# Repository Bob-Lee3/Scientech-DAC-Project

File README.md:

# Scientech-DAC-Project
Scientech DAC board prototype

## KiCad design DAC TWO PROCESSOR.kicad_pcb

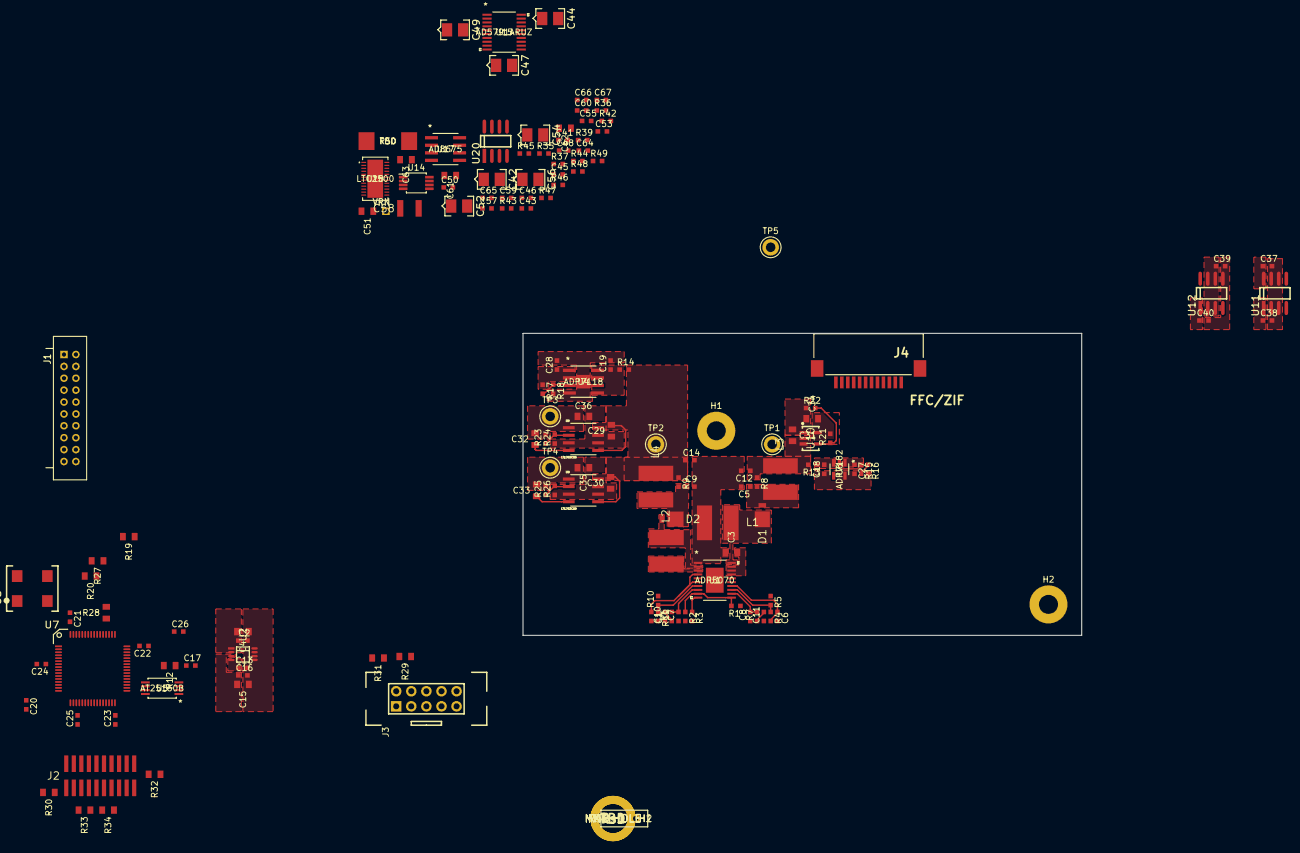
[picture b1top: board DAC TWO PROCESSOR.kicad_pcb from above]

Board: 4 copper layers, 94.0 x 50.8 mm, 155 parts (0 on the bottom side), 101 nets.

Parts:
C1, C6, C18, C19, C57, C59: 1uF; EIA0603
C2, C16, C17, C26, C41, C43, C45, C46, C48, C50, C53, C55, C64, C65, C66, C67: .1uF; EIA0603
C3, C4, C15, C34, C35, C36, C51: 10uF; EIA0805
C5, C12, C27, C28: 2.2uF; EIA0603
C7: 27pF; EIA0603
C8: 22pF; EIA0603
C9, C14, C25: 4.7uF; EIA0603
C10: .022uF; EIA0603
C11: .082uF; EIA0603
C13, C20, C21, C22, C23, C24, C60: .01uF; EIA0603
C29, C30, C31: 1uF; EIA0805
C32, C33: .01uF; EIA0805
C37, C38, C39, C40: .33uF; EIA0603
C42, C44, C47, C49, C52, C54, C56: 10uF; EIA3528
C58: 47uF X7R; EIA1210
C61, C62, C63: 6800pF; EIA0805
D1: BAT54LPS; MBRM120
D2: DFLS130-7; MBRM120
H1, H2: MNT_HOLE; HOLE188
H1#2, H2#2: MountingHole_Pad; MountingHole_3.2mm_M3_Pad
J1: CONN_20; ADAM_TECH_2FTR-20-SG
J2: CONN_10x2; SAMTEC_FTSH-110
J3: CONN_10; CON10
J4: FFC/ZIF; MOLEX_52207-1233
L1: 6.8uH; DR63
L2: 15uh; DR63
L3: 2.2uH; DR63
L4: 1.5uh; DR63
R1, R7: 30.1K; EIA0603
R2: 18.7K; EIA0603
R3: 49.9K; EIA0603
R4: 2.8K; EIA0603
R5: 54.9K; EIA0603
R6: 22K; EIA0603
R8, R13, R14: 10; EIA0603
R9: 4.7; EIA0603
R10: 63.4K; EIA0603
R11: 3.57K; EIA0603
R12: 220; EIA0805
R15, R17: 105K; EIA0603
R16, R18, R35, R36, R39, R42, R43, R44: 10K; EIA0603
R19, R20, R27, R28, R29, R30, R31, R32, R33, R34: 10K; EIA0805
R21, R25: 5.6K; EIA0603
R22, R24, R26: 1K; EIA0603
R23: 1.05K; EIA0603
R37: 5K; EIA0603
R38, R40, R41: 33; EIA0402
R45, R46: 30.1; EIA0603
R47, R48, R49: 0; EIA0603
R50: TBD; SMR3D
Rs1: TBD; Z201
TP1: VOUT2; TestPoint_Keystone_5010-5014_Multipurpose
TP2: VOUT1; TestPoint_Keystone_5010-5014_Multipurpose
TP3: +2.5V; TestPoint_Keystone_5010-5014_Multipurpose
TP4: +8V; TestPoint_Keystone_5010-5014_Multipurpose
TP5: -3V; TestPoint_Keystone_5010-5014_Multipurpose
TP7: VRN; TESTPOINT
U1: ADP5070; ADP5070AREZ
U2: REG113-3.3; REG113-33
U3: XX MHz; CB3
U4: ADP7118; ADP7118ARDZ
U5: AT25160B; AT25160B-XHL-B
U6: ADP7182; ADP7182AUJZ-2.5-R7
U7: STM32F7xx; TQFP50P-64
U8, U9: LT1763CS8; SO-8_S
U10: LT1964-SD; SOT23-5
U11: SM78L05; SOIC127P-8
U12: SM79L05; SOIC127P-8
U14: LT6655; MSOP65P-8
U15: AD5791ARUZ; AD5791BRUZ
U17: AD8675; AD8675ARZ-REEL7
U18: LTC2500; LTC2500CDKD-32-TRPBF
U20: OPA277; SOIC127P-8

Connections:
3.3V: C15.1, C16.1, C20.2, C21.2, C22.2, C24.2, C26.1, C46.2, C47.1, C60.1, J1.9, J2.1, R12.1, R20.1, U2.3, U5.7, U5.8, U7.13, U7.19, U7.32, U7.48, U7.64, U15.9, U15.10, U18.22
+2.5V: C32.1, C36.1, R23.2, TP3.1, U8.1
+5V: C38.1, J4.8, U11.1
+8V: C33.1, C35.1, R25.2, TP4.1, U9.1
+12V: C37.1, C64.1, C66.1, J1.17, J1.18, U11.8, U20.7
-3V: C34.1, R21.2, TP5.1, U10.5
-5V: C40.1, J4.10, U12.1
-12V: C39.1, C65.1, C67.1, J1.19, J1.20, U12.2, U12.3, U12.6, U12.7, U20.4
/Analog Portion/VREFN: C59.1, R44.1, TP7.1
/Analog Portion/VREFP: C57.1, C58.1, R39.1, R42.2, U18.8, U18.9
/EXT_NRST: C23.1, J2.10, U7.7
/I2C1_SCL: J3.8, R31.2, U7.58
/I2C1_SDA: J3.6, R29.2, U7.59
/JTCK_SWCLK: J2.4, U7.49
/JTDI: J2.8, U7.50
/JTDO: J2.6, U7.55
/JTMS_SWDIO: J2.2, U7.46
/NJTRST: J2.16, U7.56
/ON_~OFF: J3.10, U7.14, U7.45
/USART3_RX: J1.6, R28.2, U7.52
/USART3_TX: J1.5, R27.2, U7.51
/VOUT1: C14.1, C29.1, C30.1, L4.1, R9.1, R10.2, R14.2, TP2.1, U8.5, U8.8, U9.5, U9.8
/VOUT2: C12.1, C31.1, L3.1, R5.1, R8.1, R13.2, TP1.1, U10.2, U10.3
/~FUNCTION: J3.9, U7.44
/~MODE: J3.7, U7.43
/~SEND: J3.5, U7.42
/~ZERO: J3.3, U7.41
AGND: C1.2, C6.2, C7.1, C8.1, C10.1, C11.1, C18.2, C19.2, C27.2, C28.2, C29.2, C30.2, C31.2, C34.2, C35.2, C36.2, C37.2, C38.2, C39.2, C40.2, C41.2, C42.2, C43.2, C44.1, C45.2, C46.1, C47.2, C48.1, C49.1, C50.2, C51.2, C52.1, C53.2, C54.2, C55.2, C56.1, C57.2, C58.2, C59.2, C60.2, C61.1, C63.2, C64.2, C65.2, C66.2, C67.2, J1.1, J1.2, J1.15, J4.5, R2.2, R3.2, R11.2, R16.2, R18.2, R22.1, R24.1, R26.1, R36.2, R43.2, U1.15, U4.4, U4.EPAD, U6.5, U8.3, U8.6, U8.7, U9.3, U9.6, U9.7, U10.1, U11.2, U11.3, U11.6, U11.7, U12.5, U14.3, U14.4, U14.5, U14.8, U15.15, U15.19, U18.4, U18.7, U18.10, U18.11, U18.12, U18.23, U18.24, U18.25
AVDD: C28.1, C41.1, C42.1, C45.1, C48.2, C49.2, C53.1, C54.1, R17.1, R35.2, U4.1, U4.2, U14.2, U15.5, U17.7
AVSS: C27.1, C43.1, C44.2, C50.1, C52.2, C55.1, C56.2, R15.1, U6.1, U15.18, U17.4
BUSY: U7.24, U18.21
CM_GND: C3.2, C5.2, C9.2, C12.2, C14.2, L1.2, U1.1, U1.EPAD
DGND: C2.2, C4.2, C13.2, C15.2, C16.2, C17.2, C20.1, C21.1, C22.1, C23.2, C24.1, C25.2, C26.2, J1.13, J1.14, J2.3, J2.5, J2.9, J2.15, J2.17, J2.19, J3.1, J4.7, R30.2, R32.2, R33.2, R34.2, U2.5, U2.6, U2.7, U2.8, U3.2, U5.4, U7.12, U7.18, U7.31, U7.47, U7.63
DRL: R40.2, U7.37
FPOS: J4.9, U7.61
MCLK: U7.10, U18.13
unnamed: C1.1, U1.4, U1.6, U1.16
unnamed: C5.1, D1.2, L3.2, R8.2
unnamed: C6.1, R4.2, U1.14
unnamed: C7.2, R6.2, U1.8
unnamed: C8.2, R7.2, U1.12
unnamed: C9.1, D2.1, L4.2, R9.2
unnamed: C10.2, R6.1
unnamed: C11.2, R7.1
unnamed: C13.1, U2.4
unnamed: C17.1, R12.2, U3.4
unnamed: C18.1, R13.1, U6.3
unnamed: C19.1, R14.1, U4.5, U4.7, U4.8
unnamed: C25.1, U7.30
unnamed: C32.2, U8.4
unnamed: C33.2, U9.4
unnamed: C51.1, R37.2, U14.6, U14.7
unnamed: C61.2, C62.1, R45.2, U18.6
unnamed: C62.2, C63.1, R46.2, U18.5
unnamed: D1.1, L1.1, U1.20
unnamed: D2.2, L2.1, U1.2
unnamed: R47.2, U15.20, U17.6, U20.3
unnamed: J1.3, R19.1, R20.2
unnamed: J2.12, R34.1
unnamed: J2.14, R33.1
unnamed: J2.18, R32.1
unnamed: J2.20, R30.1
unnamed: J4.1, J4.3, R49.1
unnamed: J4.2, J4.4, R48.2, R50.1, Rs1.1, U20.2
unnamed: L2.2, U1.3
unnamed: R1.2, R2.1, U1.9, U1.11
unnamed: R3.1, U1.10
unnamed: R4.1, R5.2, U1.13
unnamed: R10.1, R11.1, U1.7
unnamed: R15.2, R16.1, U6.2
unnamed: R17.2, R18.1, U4.3
unnamed: R19.2, U7.60
unnamed: R21.1, R22.2, U10.4
unnamed: R23.1, R24.2, U8.2
unnamed: R25.1, R26.2, U9.2
unnamed: R35.1, U14.1
unnamed: R36.1, R39.2
unnamed: R38.1, U18.17
unnamed: R40.1, U18.15
unnamed: R41.1, U18.20
unnamed: R42.1, R44.2
unnamed: R47.1, R48.1, R49.2
unnamed: U3.3, U7.5
unnamed: U5.1, U5.3, U7.33
unnamed: U5.2, U7.35
unnamed: U5.5, U7.36
unnamed: U5.6, U7.34
unnamed: U15.1, U17.2
unnamed: U15.2, U17.3
PA1_NLDAC: U7.15, U15.8
PA2_NCLR: U7.16, U15.7
PA3_NRESET: U7.17, U15.6
RDLA: U7.8, U18.1
RDLB: U7.9, U18.2
SPI1_MISO: R38.2, R41.2, U7.22, U15.11
SPI1_MOSI: U7.23, U15.12, U18.16
SPI1_NSS: U7.20, U15.14
SPI1_SCK: U7.21, U15.13, U18.18, U18.19
SRGND: J1.16, R50.2, Rs1.2
SYNC: U7.11, U18.14
VCC: C2.1, C3.1, C4.1, J1.11, J1.12, J3.2, R1.1, R27.1, R28.1, R29.1, R31.1, U1.17, U1.18, U1.19, U2.1, U2.2

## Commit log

2019-11-18 Add files via upload
    Our libraries. Bob
2019-11-18 Added outline, mounting holes and annotated components.
2019-11-18 Pushing footprints
2019-11-18 BOM Tools
2019-11-18 Starting layout. Initial Commit.
2019-11-18 EOD Push.
2019-11-20 Added footprints and associations
2019-11-20 Layed out some more power rails. Need to TRIPLE check the EPAD connections. Many are incorrectly pinned.
2019-11-20 Add files via upload
    Final - added testpoints, added MANF# data. Removed reconstruction filter
2019-11-26 Added footpritn associations.
2019-11-26 Moving components around that were changed due to annotation errors.
2019-11-26 Good break point. Nearly finished ADP5070 layout. Just need uC layout and system positioning.
2019-11-27 Layout and placement of most switchers complete.
2019-11-27 Added the analog portion to the board. Added as schematic sheet.
2019-11-27 EOD Commit
2019-12-02 Moved cap for demo

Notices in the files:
parts and their libraries:
Copyright 2016 Accelerated Designs. All rights reserved.
